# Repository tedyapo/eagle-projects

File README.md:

# eagle-projects

this is my private repo of PCB designs in Eagle

you probably should not use these for anything unless I have specifically pointed you to a design

I DO NOT support this repository for anyone other than myself

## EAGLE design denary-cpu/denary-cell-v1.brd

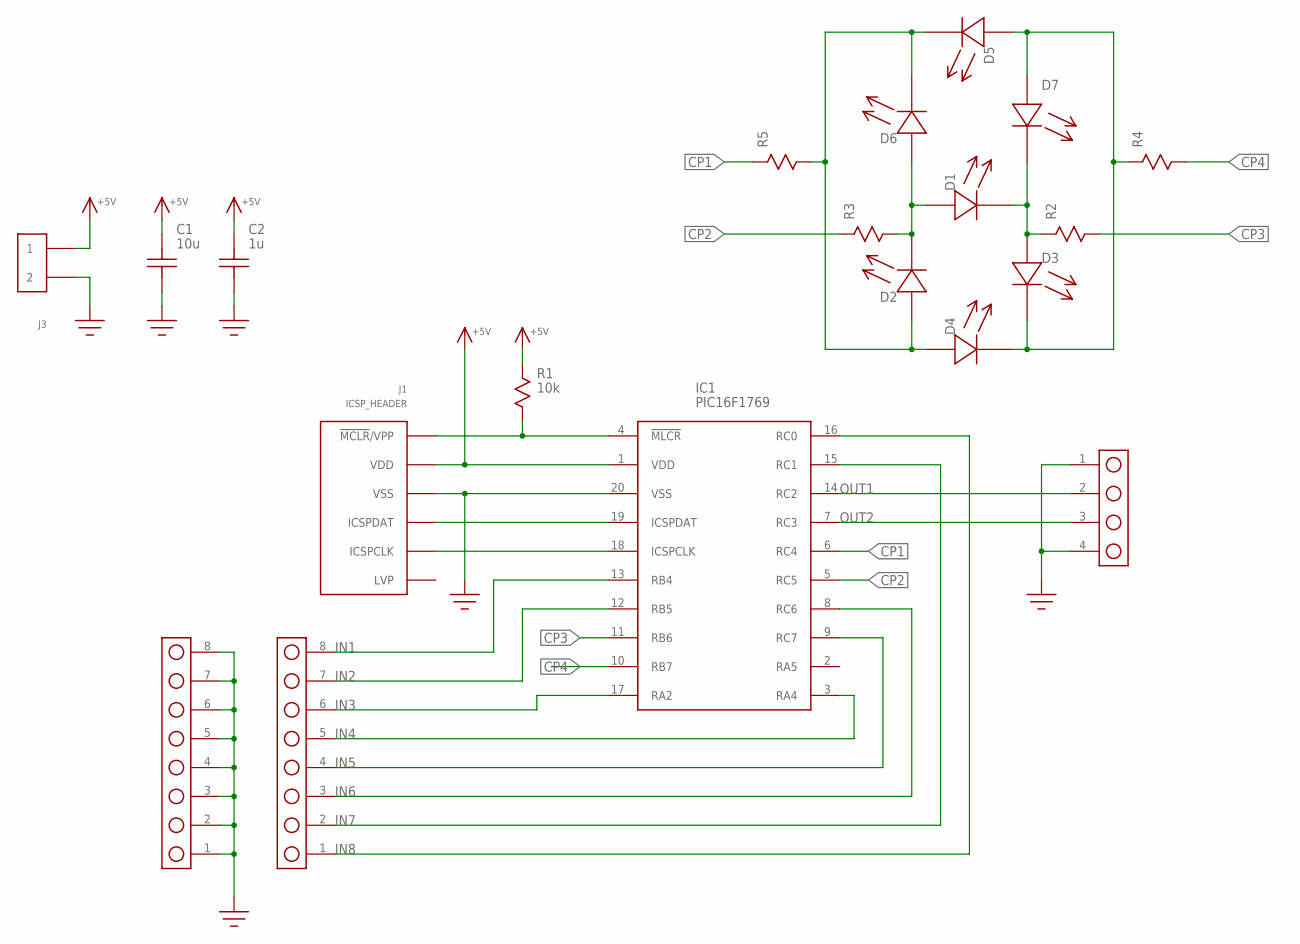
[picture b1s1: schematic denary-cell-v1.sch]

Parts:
C1: 10u; 1206
C2: 1u; C0603
D1, D2, D3, D4, D5, D6, D7: LED; LED_0603
IC1: PIC16F1769; SOIC-20W
J1: ICSP_HEADER; HEADER_6PIN
J2: HEADER_4PIN
J3: HEADER_2PIN
J4, J5: HEADER_8PIN; HEADER_8_PIN
R1: 10k; R0603
R2, R3, R4, R5: R0603

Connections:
+5V: C1.P$2, C2.P$2, IC1.1 (VDD), J1.2 (VDD), J3.1, R1.P$1
CP1: IC1.6 (RC4), R5.P$1
CP2: IC1.5 (RC5), R3.P$1
CP3: IC1.11 (RB6), R2.P$2
CP4: IC1.10 (RB7), R4.P$2
GND: C1.P$1, C2.P$1, IC1.20 (VSS), J1.3 (VSS), J2.1, J2.4, J3.2, J5.1, J5.2, J5.3, J5.4, J5.5, J5.6, J5.7, J5.8
IN1: IC1.13 (RB4), J4.8
IN2: IC1.12 (RB5), J4.7
IN3: IC1.17 (RA2), J4.6
IN4: IC1.3 (RA4), J4.5
IN5: IC1.9 (RC7), J4.4
IN6: IC1.8 (RC6), J4.3
IN7: IC1.15 (RC1), J4.2
IN8: IC1.16 (RC0), J4.1
unnamed: IC1.4 (!MLCR!), J1.1 (!MCLR!/VPP), R1.P$2
unnamed: D2.A, D4.A, D5.C, D6.C, R5.P$2
unnamed: IC1.19 (ICSPDAT), J1.4 (ICSPDAT)
unnamed: IC1.18 (ICSPCLK), J1.5 (ICSPCLK)
unnamed: D1.A, D2.C, D6.A, R3.P$2
unnamed: D1.C, D3.A, D7.C, R2.P$1
unnamed: D3.C, D4.C, D5.A, D7.A, R4.P$1
OUT1: IC1.14 (RC2), J2.2
OUT2: IC1.7 (RC3), J2.3

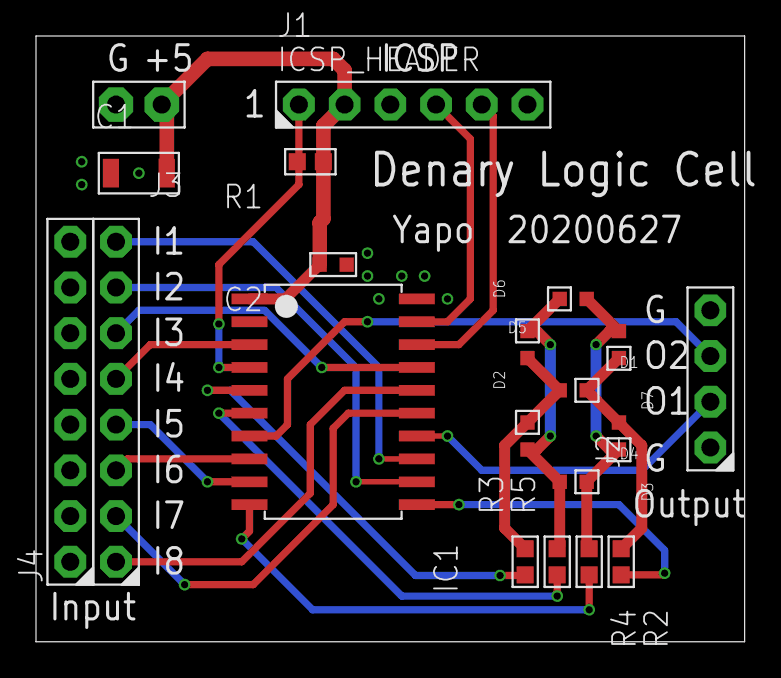
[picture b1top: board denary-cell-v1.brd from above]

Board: 2 copper layers, 39.4 x 33.7 mm, 20 parts (0 on the bottom side), 23 nets.

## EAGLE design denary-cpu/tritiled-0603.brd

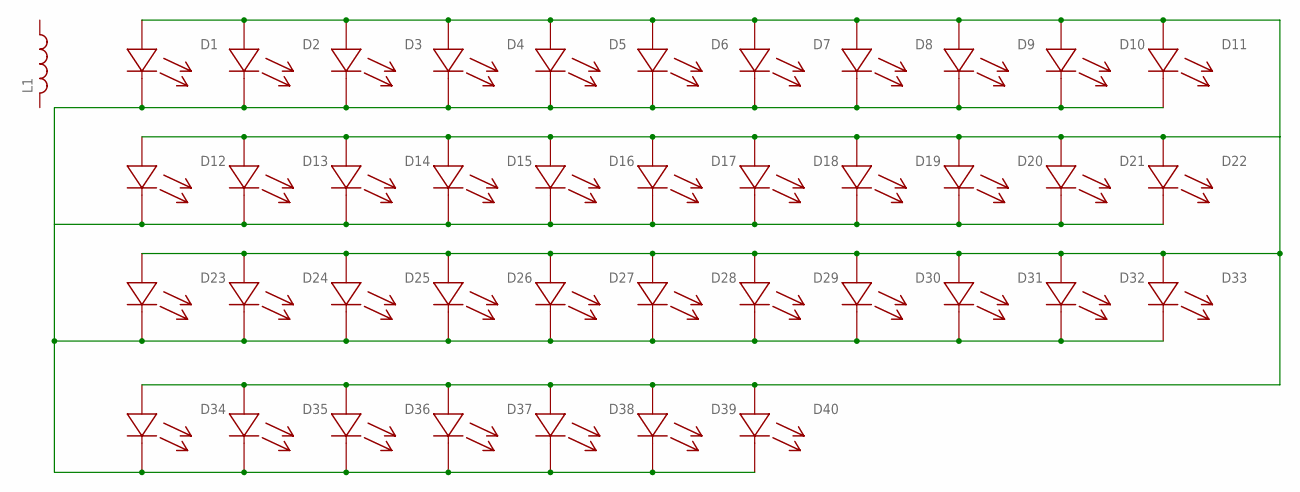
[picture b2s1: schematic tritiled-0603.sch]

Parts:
D1, D2, D3, D4, D5, D6, D7, D8, D9, D10, D11, D12, D13, D14, D15, D16, D17, D18, D19, D20, D21, D22, D23, D24, D25, D26, D27, D28, D29, D30, D31, D32, D33, D34, D35, D36, D37, D38, D39, D40: LED; LED_0603
L1: SRR6028_INDUCTOR

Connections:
unnamed: D1.C, D2.C, D3.C, D4.C, D5.C, D6.C, D7.C, D8.C, D9.C, D10.C, D11.C, D12.C, D13.C, D14.C, D15.C, D16.C, D17.C, D18.C, D19.C, D20.C, D21.C, D22.C, D23.C, D24.C, D25.C, D26.C, D27.C, D28.C, D29.C, D30.C, D31.C, D32.C, D33.C, D34.C, D35.C, D36.C, D37.C, D38.C, D39.C, D40.C
unnamed: D1.A, D2.A, D3.A, D4.A, D5.A, D6.A, D7.A, D8.A, D9.A, D10.A, D11.A, D12.A, D13.A, D14.A, D15.A, D16.A, D17.A, D18.A, D19.A, D20.A, D21.A, D22.A, D23.A, D24.A, D25.A, D26.A, D27.A, D28.A, D29.A, D30.A, D31.A, D32.A, D33.A, D34.A, D35.A, D36.A, D37.A, D38.A, D39.A, D40.A

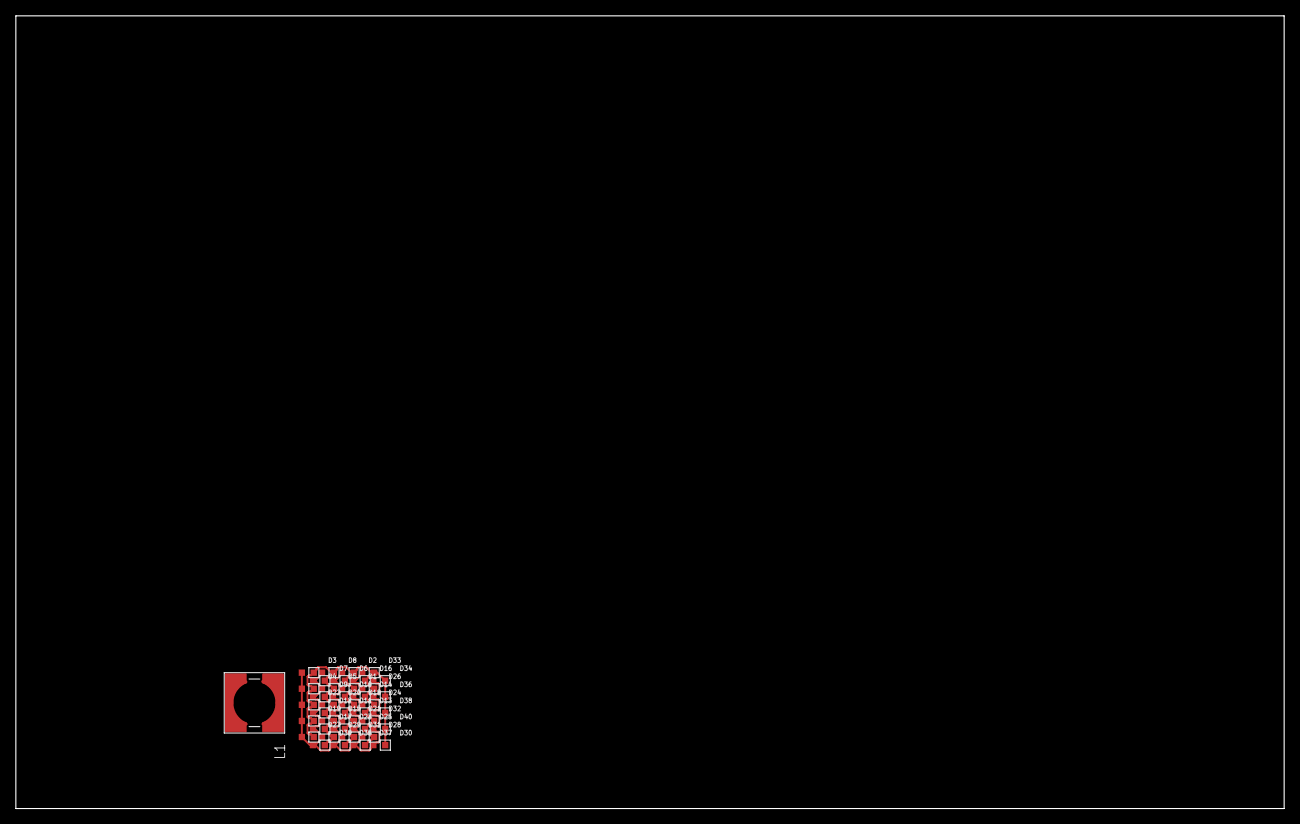
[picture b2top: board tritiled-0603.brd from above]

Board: 2 copper layers, 160.0 x 100.0 mm, 41 parts (0 on the bottom side), 2 nets.

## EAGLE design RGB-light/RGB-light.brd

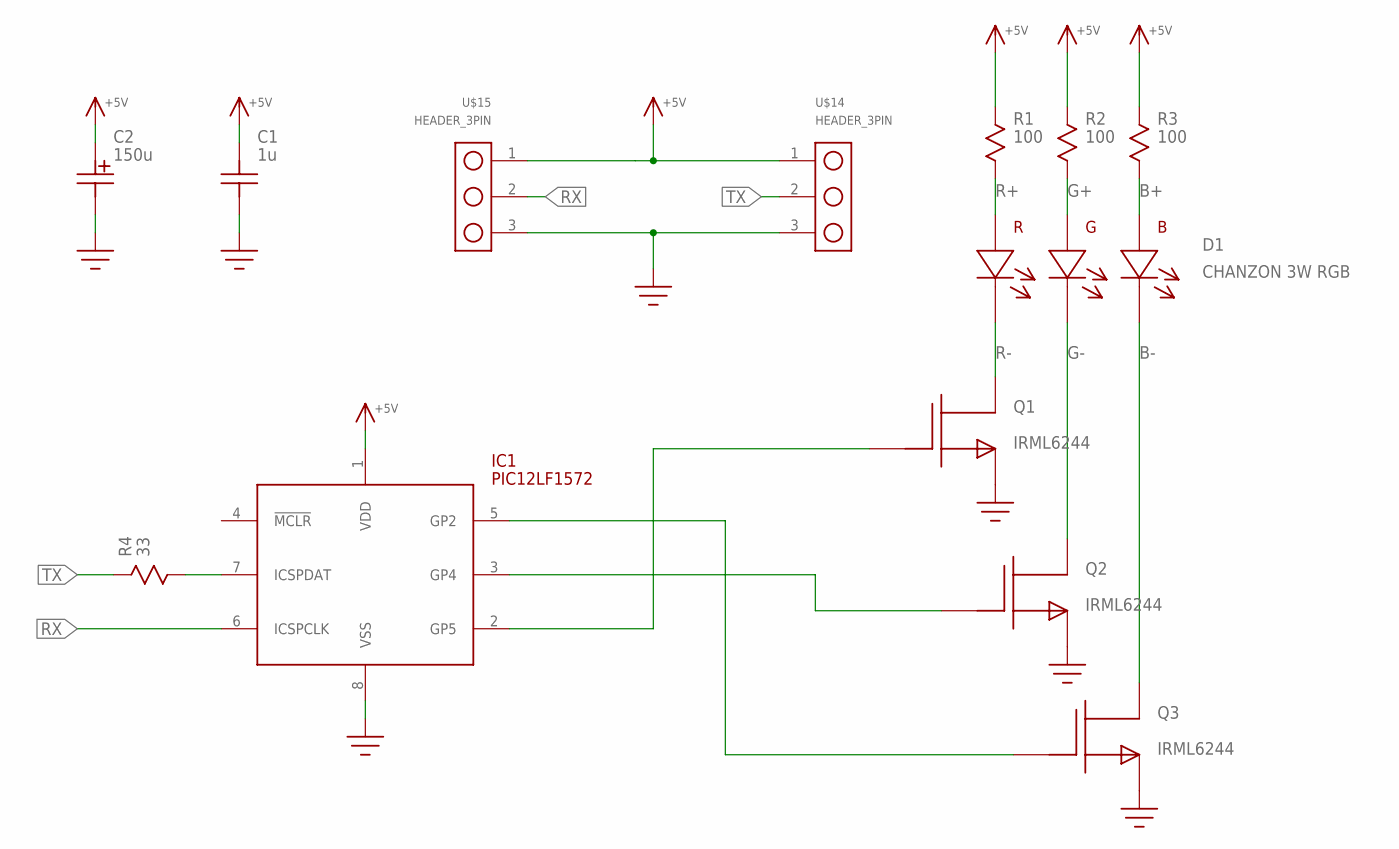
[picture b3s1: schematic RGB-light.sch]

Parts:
C1: 1u; C0603
C2: 150u; C-TANTALUM-CODE-C
D1: CHANZON 3W RGB; LED_3W_RGB
IC1: PIC12LF1572; SOIC8
Q1, Q2, Q3: IRML6244; SOT-23
R1, R2, R3: 100; R1206
R4: 33; R0603
U$14, U$15: HEADER_3PIN

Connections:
+5V: C1.P$2, C2.+, IC1.1 (VDD), R1.P$1, R2.P$1, R3.P$1, U$14.1, U$15.1
B+: D1.B+ (B-A), R3.P$2
B-: D1.B- (B-C), Q3.3 (D)
G+: D1.G+ (G-A), R2.P$2
G-: D1.G- (G-C), Q2.3 (D)
GND: C1.P$1, C2.-, IC1.8 (VSS), Q1.2 (S), Q2.2 (S), Q3.2 (S), U$14.3, U$15.3
unnamed: IC1.7 (ICSPDAT), R4.P$2
unnamed: IC1.5 (GP2), Q3.1 (G)
unnamed: IC1.3 (GP4), Q2.1 (G)
unnamed: IC1.2 (GP5), Q1.1 (G)
R+: D1.R+ (R-A), R1.P$2
R-: D1.R- (R-C), Q1.3 (D)
RX: IC1.6 (ICSPCLK), U$15.2
TX: R4.P$1, U$14.2

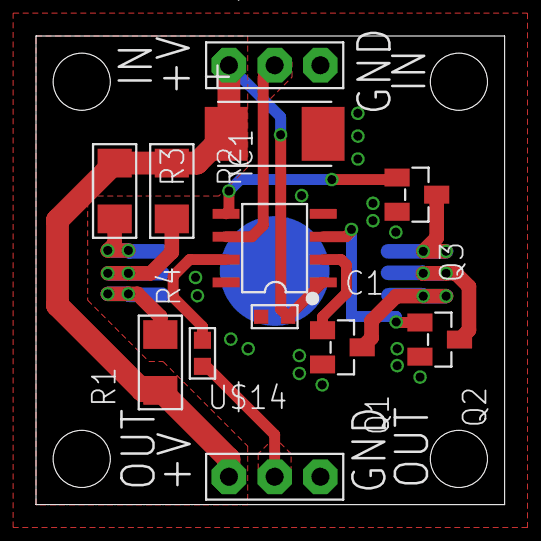
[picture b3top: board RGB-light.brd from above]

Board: 2 copper layers, 26.0 x 26.0 mm, 13 parts (1 on the bottom side), 14 nets.

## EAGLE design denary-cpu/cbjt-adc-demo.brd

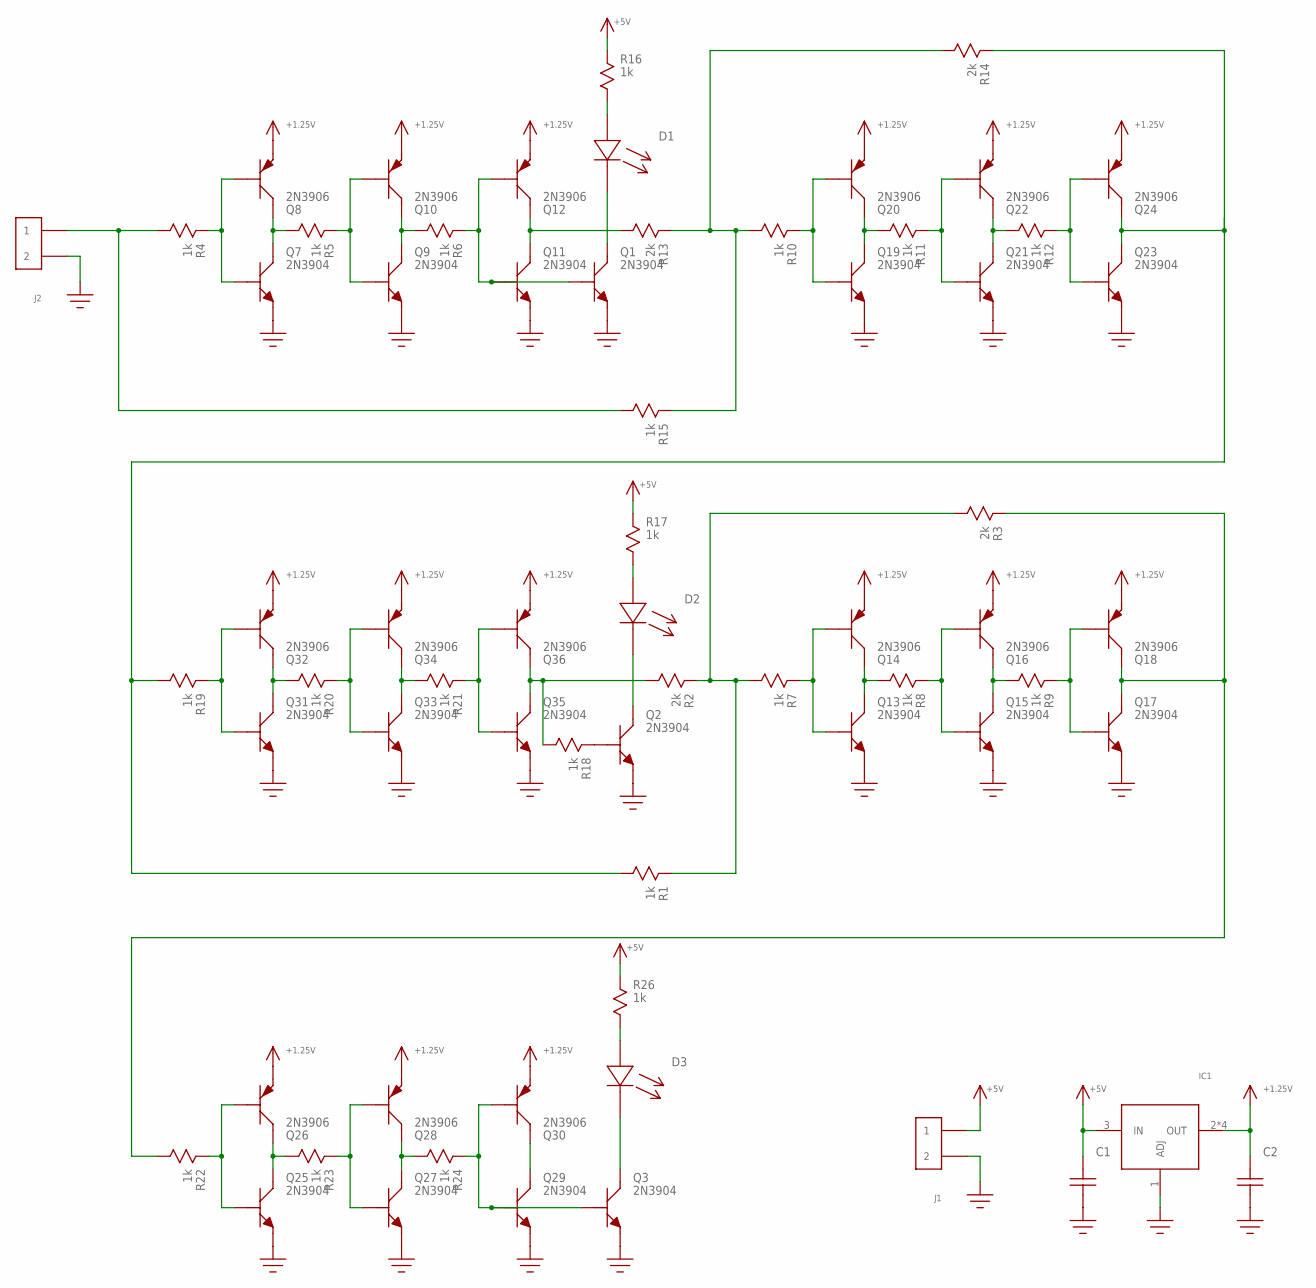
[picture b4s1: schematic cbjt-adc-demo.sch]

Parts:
C1, C2: C100MIL; C-100MIL
D1, D2, D3: LED5MM; LED-5MM
IC1: LM317; TO-220
J1, J2: HEADER_2PIN
Q1, Q2, Q3, Q7, Q9, Q11, Q13, Q15, Q17, Q19, Q21, Q23, Q25, Q27, Q29, Q31, Q33, Q35: 2N3904; TO-92
Q8, Q10, Q12, Q14, Q16, Q18, Q20, Q22, Q24, Q26, Q28, Q30, Q32, Q34, Q36: 2N3906; TO-92
R1, R4, R5, R6, R7, R8, R9, R10, R11, R12, R15, R16, R17, R18, R19, R20, R21, R22, R23, R24, R26: 1k; R-0.25W
R2, R3, R13, R14: 2k; R-0.25W

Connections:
+1.25V: C2.P$2, IC1.2 (OUT), IC1.HS@1 (OUT), IC1.HS@2 (OUT), IC1.HS@3 (OUT), Q8.1 (E), Q10.1 (E), Q12.1 (E), Q14.1 (E), Q16.1 (E), Q18.1 (E), Q20.1 (E), Q22.1 (E), Q24.1 (E), Q26.1 (E), Q28.1 (E), Q30.1 (E), Q32.1 (E), Q34.1 (E), Q36.1 (E)
+5V: C1.P$2, IC1.3 (IN), J1.1, R16.P$1, R17.P$1, R26.P$1
GND: C1.P$1, C2.P$1, IC1.1 (ADJ), J1.2, J2.2, Q1.1 (E), Q2.1 (E), Q3.1 (E), Q7.1 (E), Q9.1 (E), Q11.1 (E), Q13.1 (E), Q15.1 (E), Q17.1 (E), Q19.1 (E), Q21.1 (E), Q23.1 (E), Q25.1 (E), Q27.1 (E), Q29.1 (E), Q31.1 (E), Q33.1 (E), Q35.1 (E)
unnamed: R1.P$1, R2.P$1, R3.P$2, R7.P$2
unnamed: D1.C, Q1.3 (C)
unnamed: D1.A, R16.P$2
unnamed: Q2.2 (B), R18.P$1
unnamed: D2.C, Q2.3 (C)
unnamed: D2.A, R17.P$2
unnamed: Q7.3 (C), Q8.3 (C), R5.P$2
unnamed: Q7.2 (B), Q8.2 (B), R4.P$1
unnamed: Q9.3 (C), Q10.3 (C), R6.P$2
unnamed: Q9.2 (B), Q10.2 (B), R5.P$1
unnamed: Q11.3 (C), Q12.3 (C), R13.P$2
unnamed: Q1.2 (B), Q11.2 (B), Q12.2 (B), R6.P$1
unnamed: Q13.3 (C), Q14.3 (C), R8.P$2
unnamed: Q13.2 (B), Q14.2 (B), R7.P$1
unnamed: Q15.3 (C), Q16.3 (C), R9.P$2
unnamed: Q15.2 (B), Q16.2 (B), R8.P$1
unnamed: Q17.3 (C), Q18.3 (C), R3.P$1, R22.P$2
unnamed: Q17.2 (B), Q18.2 (B), R9.P$1
unnamed: Q19.3 (C), Q20.3 (C), R11.P$2
unnamed: Q19.2 (B), Q20.2 (B), R10.P$1
unnamed: Q21.3 (C), Q22.3 (C), R12.P$2
unnamed: Q21.2 (B), Q22.2 (B), R11.P$1
unnamed: Q23.3 (C), Q24.3 (C), R1.P$2, R14.P$1, R19.P$2
unnamed: Q23.2 (B), Q24.2 (B), R12.P$1
unnamed: R10.P$2, R13.P$1, R14.P$2, R15.P$1
unnamed: J2.1, R4.P$2, R15.P$2
unnamed: Q25.3 (C), Q26.3 (C), R23.P$2
unnamed: Q25.2 (B), Q26.2 (B), R22.P$1
unnamed: Q27.3 (C), Q28.3 (C), R24.P$2
unnamed: Q27.2 (B), Q28.2 (B), R23.P$1
unnamed: Q29.3 (C), Q30.3 (C)
unnamed: Q3.2 (B), Q29.2 (B), Q30.2 (B), R24.P$1
unnamed: Q31.3 (C), Q32.3 (C), R20.P$2
unnamed: Q31.2 (B), Q32.2 (B), R19.P$1
unnamed: Q33.3 (C), Q34.3 (C), R21.P$2
unnamed: Q33.2 (B), Q34.2 (B), R20.P$1
unnamed: Q35.3 (C), Q36.3 (C), R2.P$2, R18.P$2
unnamed: Q35.2 (B), Q36.2 (B), R21.P$1
unnamed: D3.C, Q3.3 (C)
unnamed: D3.A, R26.P$2

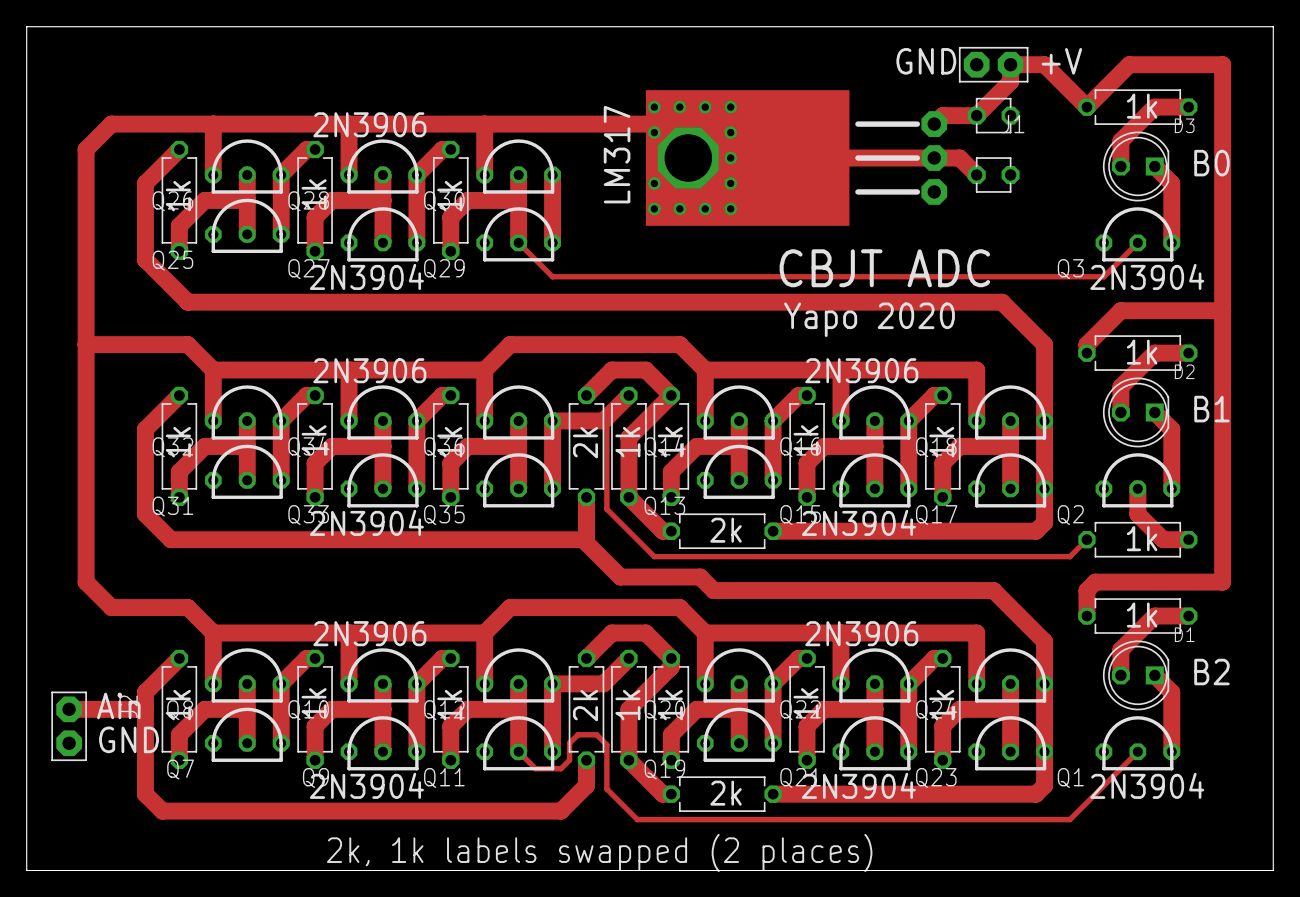
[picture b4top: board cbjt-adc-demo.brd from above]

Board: 2 copper layers, 93.3 x 63.2 mm, 66 parts (0 on the bottom side), 43 nets.

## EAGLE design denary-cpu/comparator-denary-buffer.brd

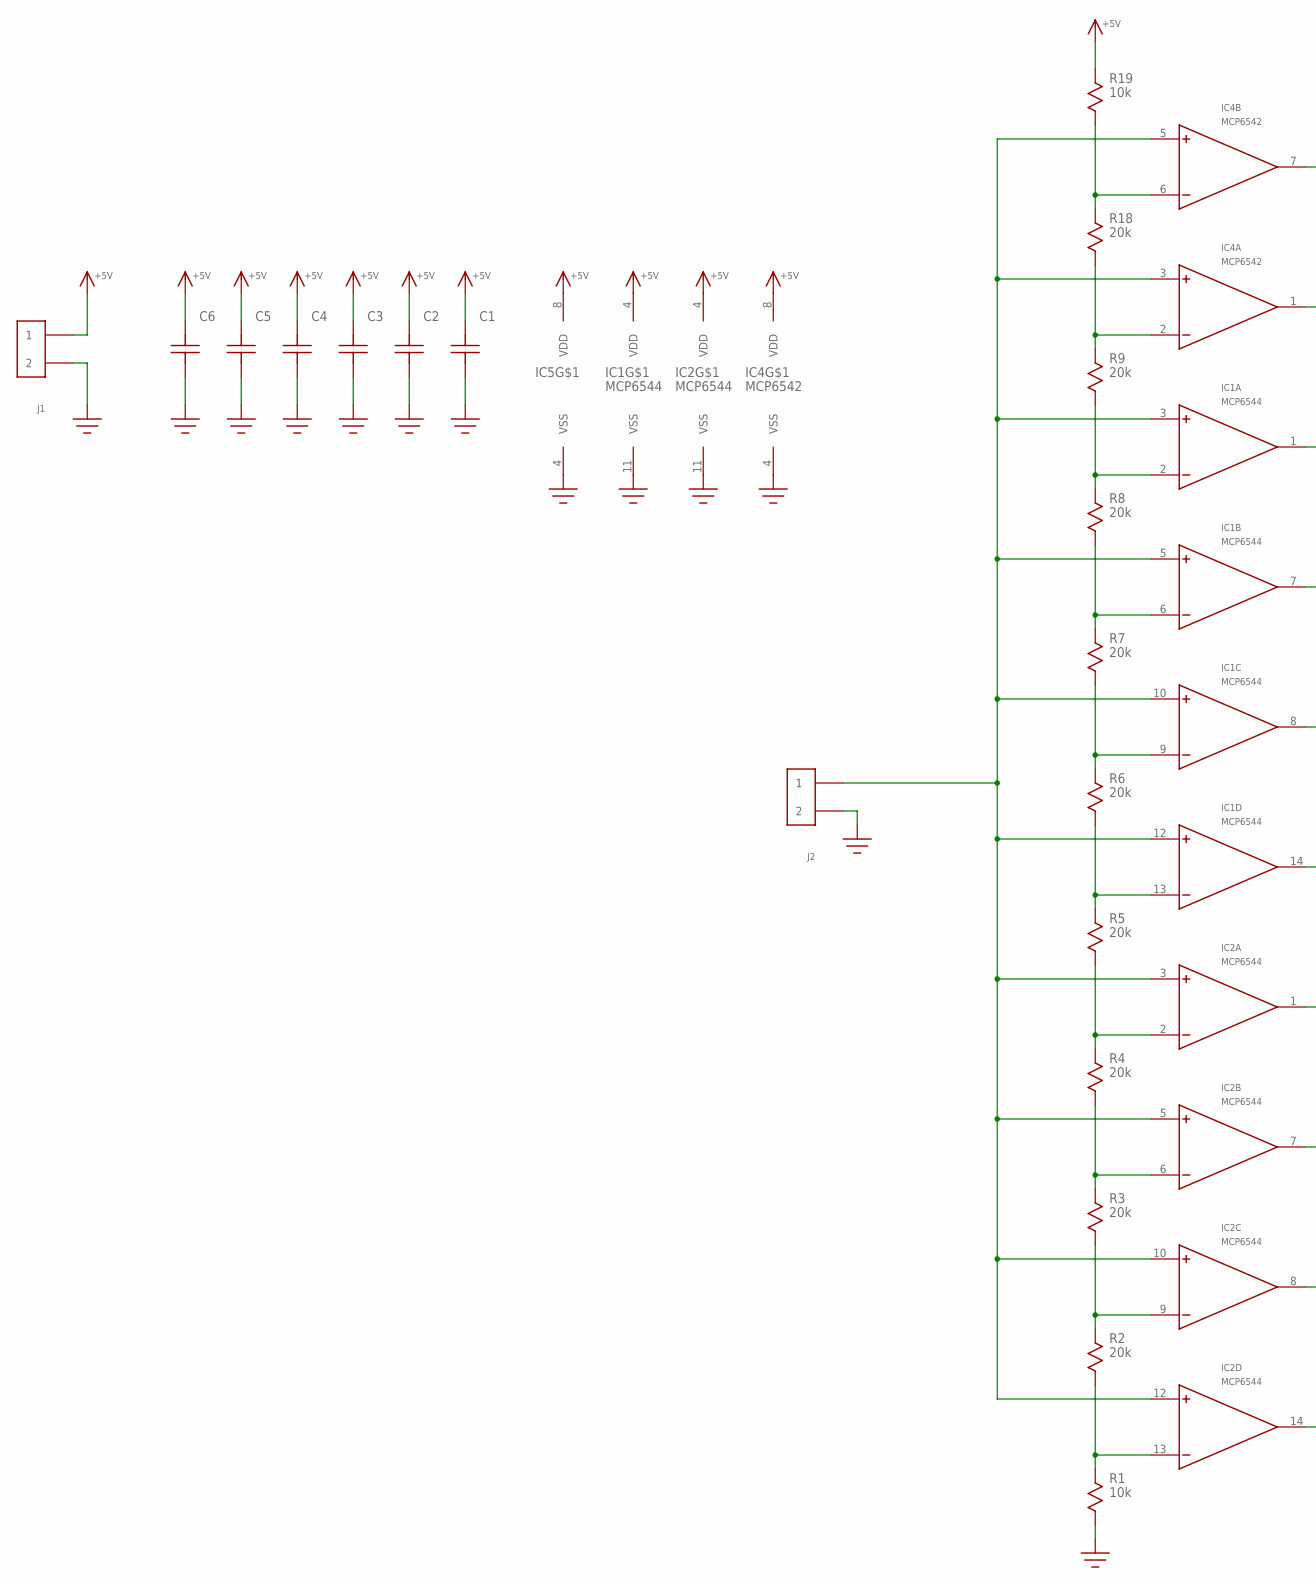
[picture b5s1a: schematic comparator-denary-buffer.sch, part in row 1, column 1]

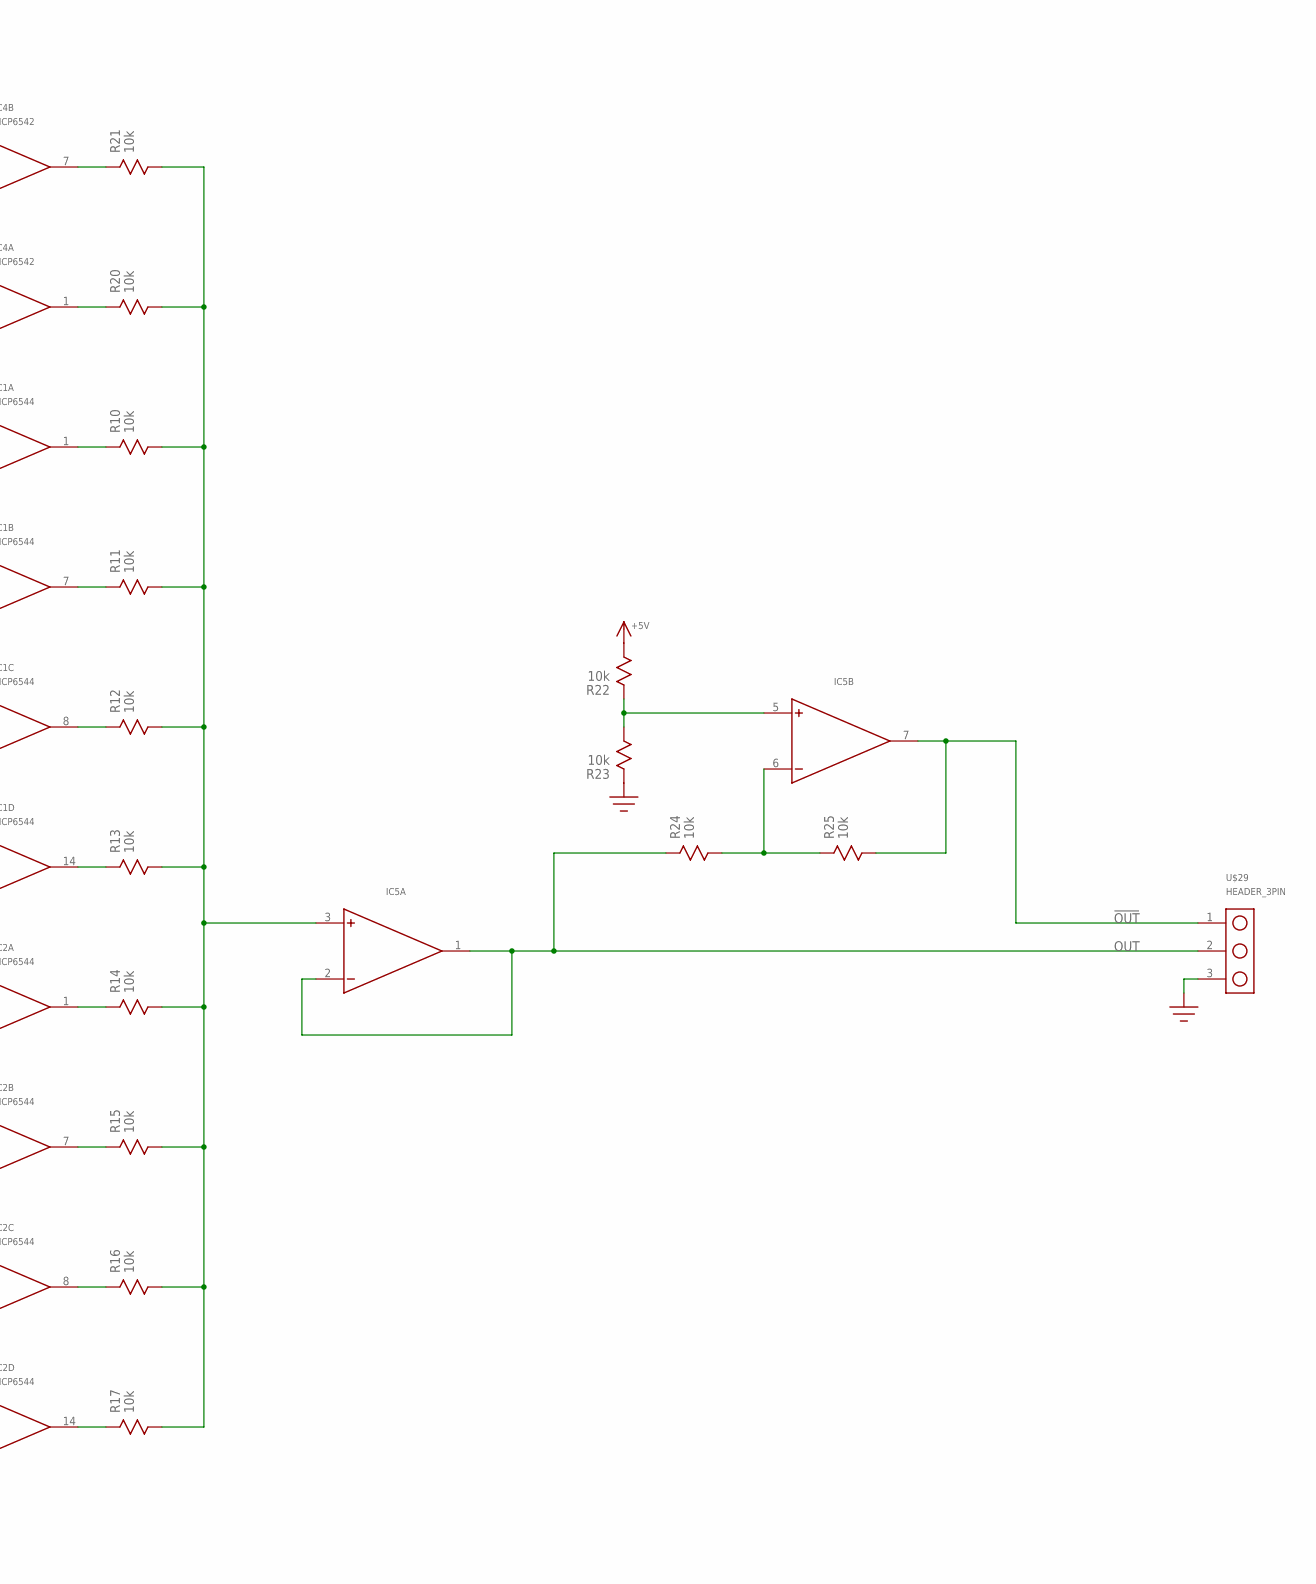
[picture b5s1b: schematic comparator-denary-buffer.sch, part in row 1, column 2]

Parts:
C1, C2, C3, C4, C5: C0603
C6: C1206; 1206
IC1, IC2: MCP6544; SOIC-14
IC4: MCP6542; SOIC8
IC5: MCP6L02; SOIC8
J1, J2: HEADER_2PIN
R1, R10, R11, R12, R13, R14, R15, R16, R17, R19, R20, R21, R22, R23, R24, R25: 10k; R0603
R2, R3, R4, R5, R6, R7, R8, R9, R18: 20k; R0603
U$29: HEADER_3PIN

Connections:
!OUT!: IC5.7 (OUT), R25.P$2, U$29.1
+5V: C1.P$2, C2.P$2, C3.P$2, C4.P$2, C5.P$2, C6.P$2, IC1.4 (VDD), IC2.4 (VDD), IC4.8 (VDD), IC5.8 (VDD), J1.1, R19.P$1, R22.P$2
GND: C1.P$1, C2.P$1, C3.P$1, C4.P$1, C5.P$1, C6.P$1, IC1.11 (VSS), IC2.11 (VSS), IC4.4 (VSS), IC5.4 (VSS), J1.2, J2.2, R1.P$2, R23.P$1, U$29.3
unnamed: IC2.13 (-), R1.P$1, R2.P$2
unnamed: IC2.14 (OUT), R17.P$1
unnamed: IC2.9 (-), R2.P$1, R3.P$2
unnamed: IC2.8 (OUT), R16.P$1
unnamed: IC2.6 (-), R3.P$1, R4.P$2
unnamed: IC2.2 (-), R4.P$1, R5.P$2
unnamed: IC1.13 (-), R5.P$1, R6.P$2
unnamed: IC1.9 (-), R6.P$1, R7.P$2
unnamed: IC1.6 (-), R7.P$1, R8.P$2
unnamed: IC2.7 (OUT), R15.P$1
unnamed: IC2.1 (OUT), R14.P$1
unnamed: IC1.14 (OUT), R13.P$1
unnamed: IC1.8 (OUT), R12.P$1
unnamed: IC1.2 (-), R8.P$1, R9.P$2
unnamed: IC1.7 (OUT), R11.P$1
unnamed: IC1.1 (OUT), R10.P$1
unnamed: IC5.3 (+), R10.P$2, R11.P$2, R12.P$2, R13.P$2, R14.P$2, R15.P$2, R16.P$2, R17.P$2, R20.P$2, R21.P$2
unnamed: IC4.2 (-), R9.P$1, R18.P$2
unnamed: IC4.6 (-), R18.P$1, R19.P$2
unnamed: IC4.7 (OUT), R21.P$1
unnamed: IC4.1 (OUT), R20.P$1
unnamed: IC5.5 (+), R22.P$1, R23.P$2
unnamed: IC5.6 (-), R24.P$2, R25.P$1
OUT: IC5.1 (OUT), IC5.2 (-), R24.P$1, U$29.2
VIN: IC1.3 (+), IC1.5 (+), IC1.10 (+), IC1.12 (+), IC2.3 (+), IC2.5 (+), IC2.10 (+), IC2.12 (+), IC4.3 (+), IC4.5 (+), J2.1

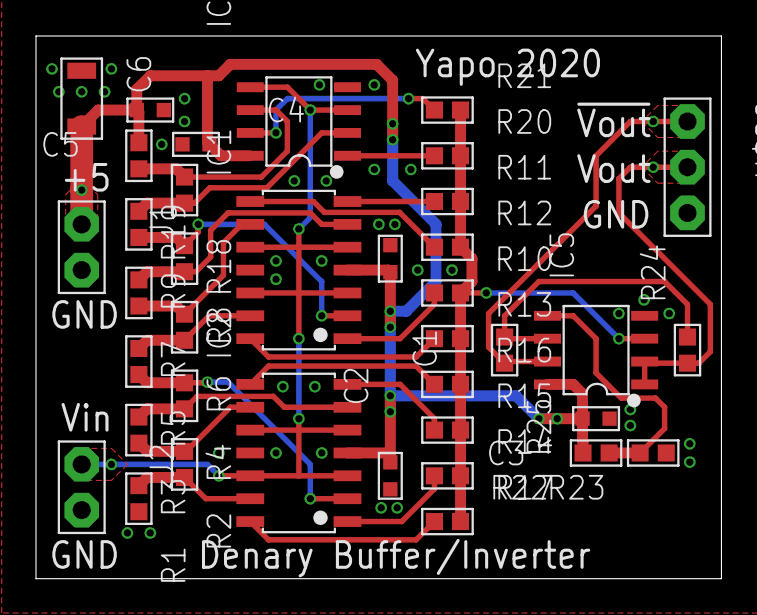
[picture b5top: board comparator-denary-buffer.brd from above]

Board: 2 copper layers, 38.1 x 30.1 mm, 38 parts (0 on the bottom side), 28 nets.

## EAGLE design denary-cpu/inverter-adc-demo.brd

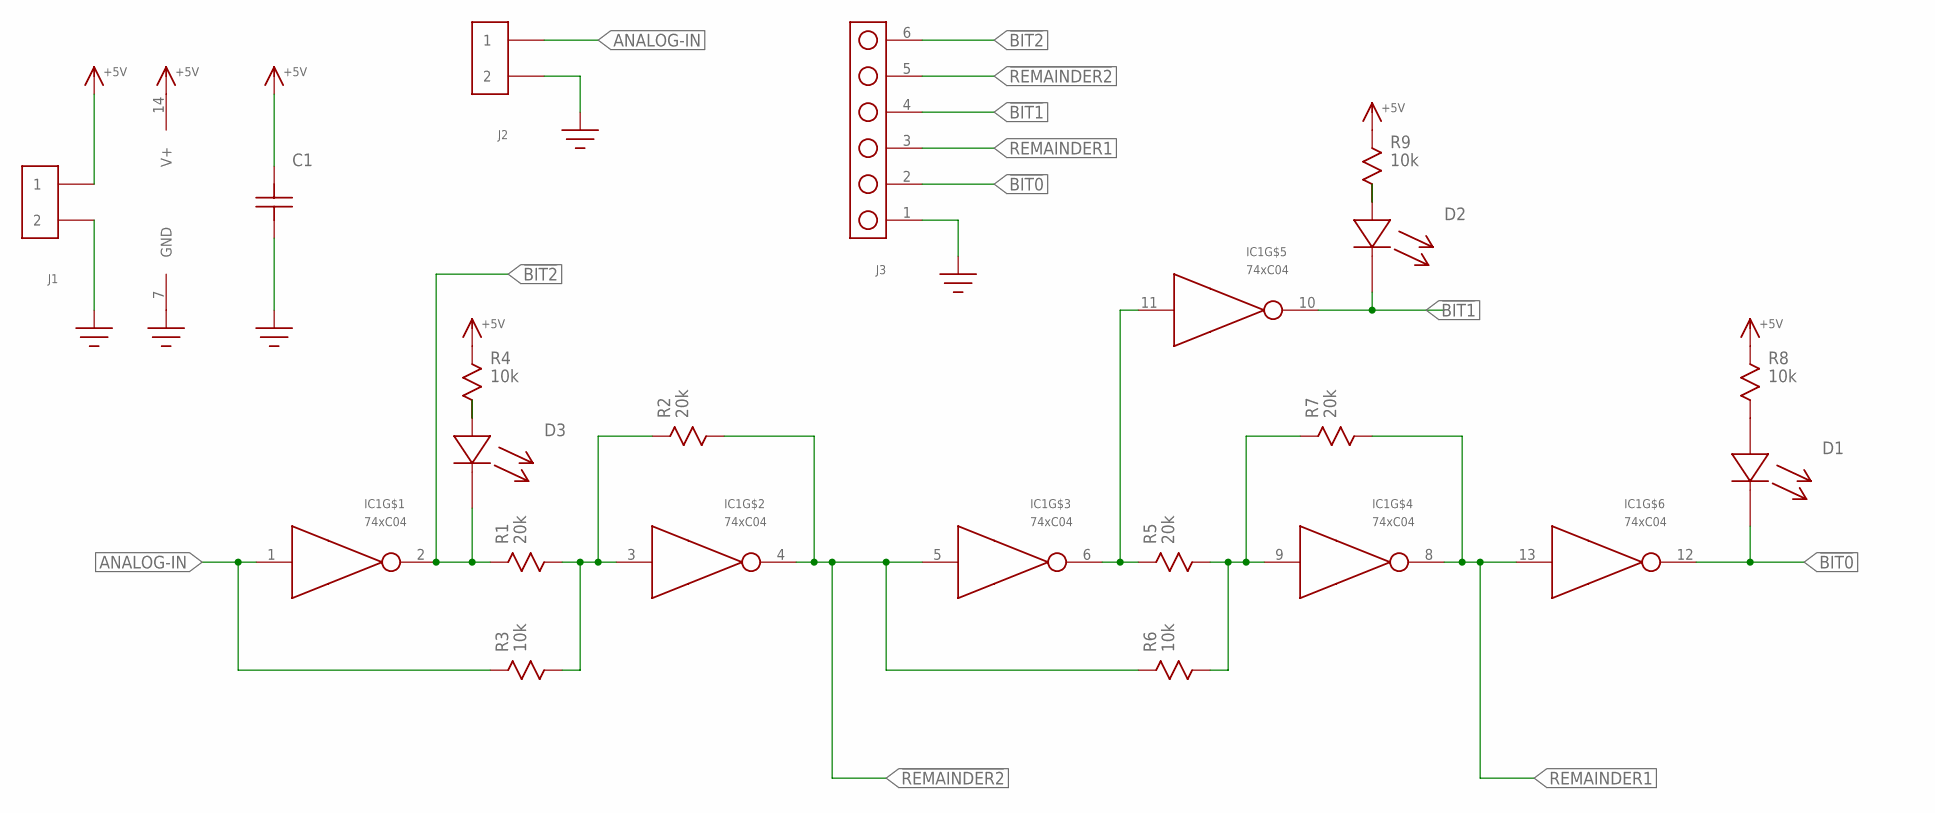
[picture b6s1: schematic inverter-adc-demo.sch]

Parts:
C1: C100MIL; C-100MIL
D1, D2, D3: LED5MM; LED-5MM
IC1: 74xC04; DIP14
J1, J2: HEADER_2PIN
J3: HEADER_6PIN
R1, R2, R5, R7: 20k; R-0.25W
R3, R4, R6, R8, R9: 10k; R-0.25W

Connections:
!BIT0!: D1.C, IC1.12 (OUT), J3.2
!BIT1!: D2.C, IC1.10 (OUT), J3.4
!BIT2!: D3.C, IC1.2 (OUT), J3.6, R1.P$1
!REMAINDER2!: IC1.4 (OUT), IC1.5 (IN), J3.5, R2.P$2, R6.P$1
+5V: C1.P$2, IC1.14 (V+), J1.1, R4.P$1, R8.P$1, R9.P$1
ANALOG-IN: IC1.1 (IN), J2.1, R3.P$1
GND: C1.P$1, IC1.7 (GND), J1.2, J2.2, J3.1
unnamed: IC1.3 (IN), R1.P$2, R2.P$1, R3.P$2
unnamed: IC1.6 (OUT), IC1.11 (IN), R5.P$1
unnamed: IC1.9 (IN), R5.P$2, R6.P$2, R7.P$1
unnamed: D3.A, R4.P$2
unnamed: D1.A, R8.P$2
unnamed: D2.A, R9.P$2
REMAINDER1: IC1.8 (OUT), IC1.13 (IN), J3.3, R7.P$2

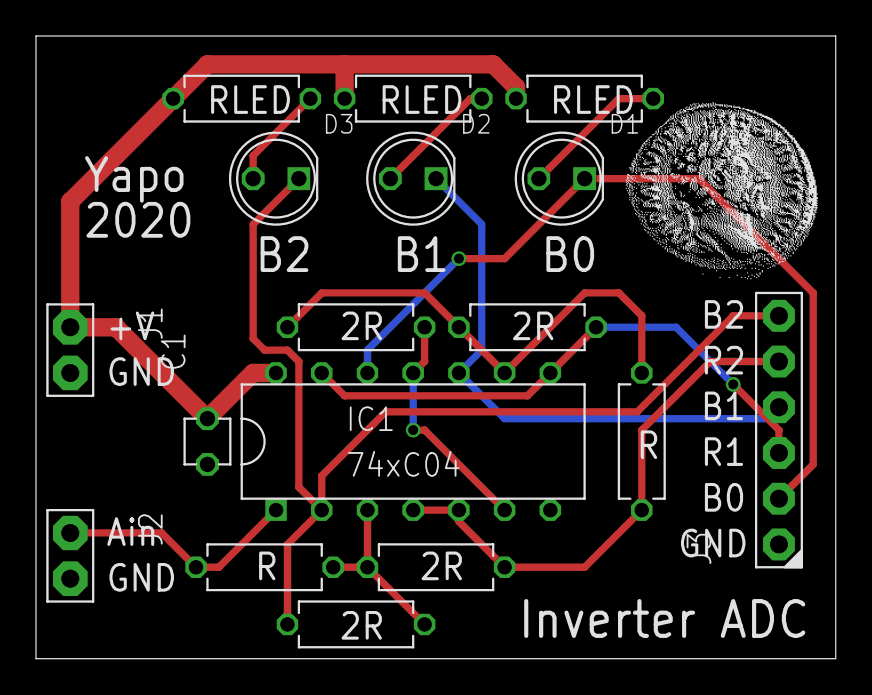
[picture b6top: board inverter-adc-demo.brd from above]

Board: 2 copper layers, 44.4 x 34.6 mm, 17 parts (0 on the bottom side), 14 nets.

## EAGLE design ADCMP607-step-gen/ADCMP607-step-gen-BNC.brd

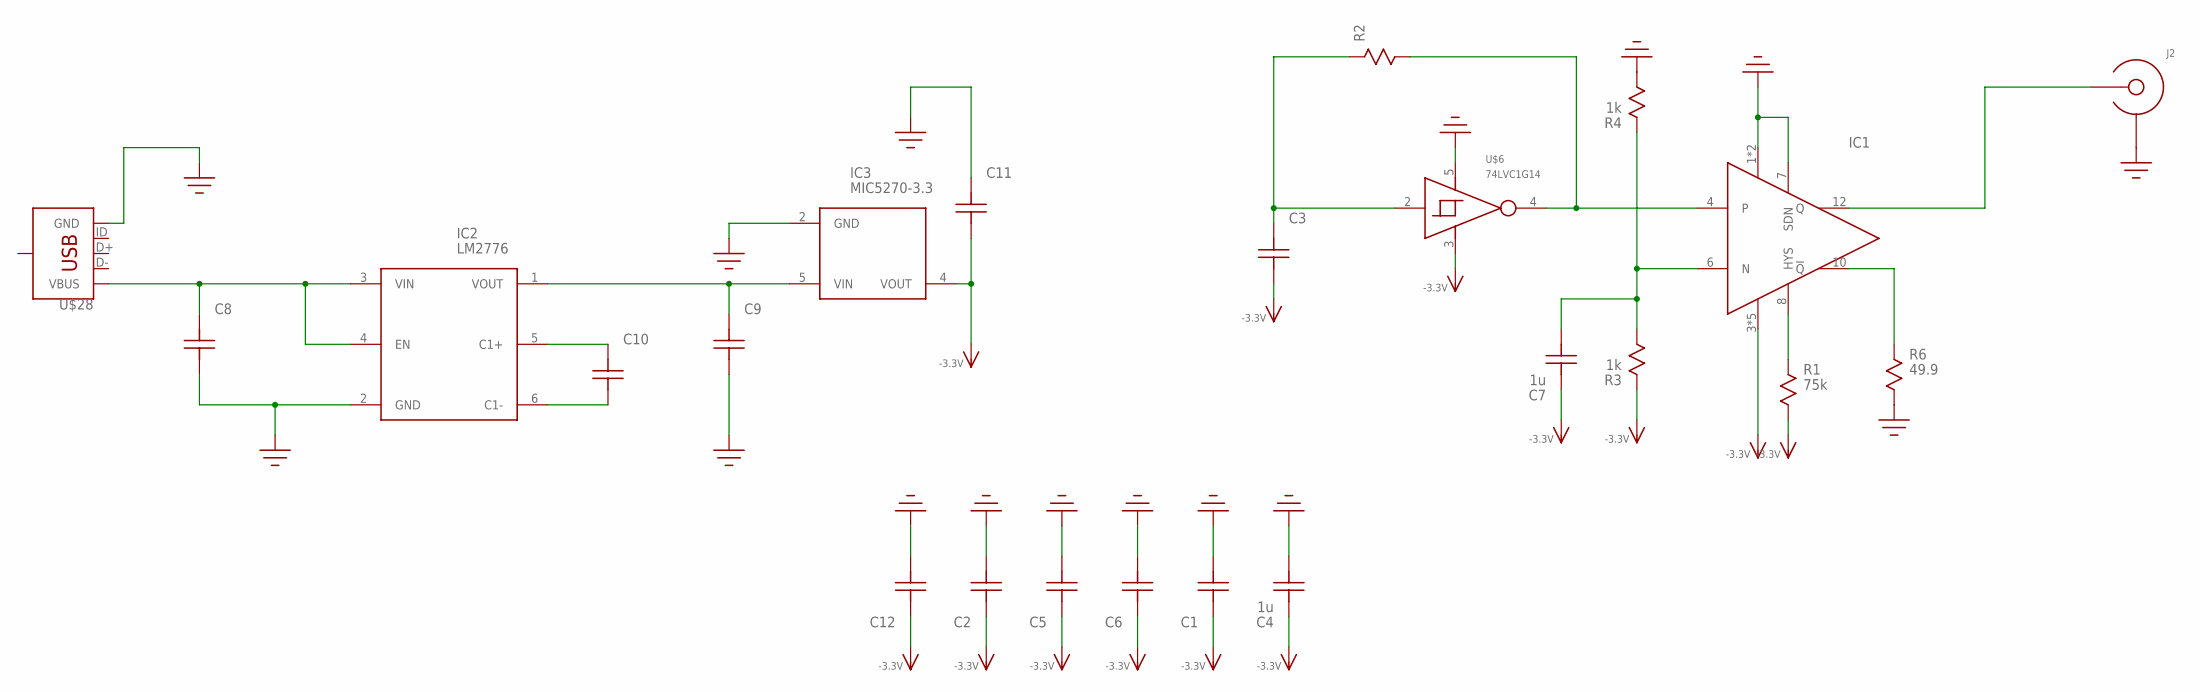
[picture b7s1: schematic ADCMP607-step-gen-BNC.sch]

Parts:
C1, C2, C3, C5, C6, C10, C12: C0603
C4, C7: 1u; C0603
C8, C9, C11: C1206; 1206
IC1: ADCMP607; QFN12-3X3
IC2: LM2776; SOT23-6
IC3: MIC5270-3.3; SOT23-5
J2: BNC_MALE_PCB
R1: 75k; R0603
R2: R0603
R3, R4: 1k; R0603
R6: 49.9; R0603
U$6: 74LVC1G14; SOT23-5
U$28: USB_MICRO_LEGS; USB_MICRO_LEGS_2

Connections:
-3.3V: C1.P$2, C2.P$2, C3.P$1, C4.P$2, C5.P$2, C6.P$2, C7.P$2, C11.P$1, C12.P$2, IC1.3 (VEE), IC1.5 (VEE), IC1.9 (VEE), IC1.11 (VEE), IC1.EP (VEE), IC3.4 (VOUT), R1.P$2, R3.P$1, U$6.3 (GND)
GND: C1.P$1, C2.P$1, C4.P$1, C5.P$1, C6.P$1, C8.P$1, C9.P$1, C11.P$2, C12.P$1, IC1.1 (VCC), IC1.2 (VCC), IC1.7 (SDN), IC2.2 (GND), IC3.2 (GND), J2.SHIELD@1 (SHIELD), J2.SHIELD@2 (SHIELD), J2.SHIELD@3 (SHIELD), J2.SHIELD@4 (SHIELD), R4.P$2, R6.P$2, U$6.5 (VCC), U$28.GND
unnamed: IC1.4, R2.P$2, U$6.4 (OUT)
unnamed: IC1.8 (HYS), R1.P$1
unnamed: IC1.12 (Q), J2.CENTER
unnamed: IC1.10 (!Q!), R6.P$1
unnamed: C3.P$2, R2.P$1, U$6.2 (IN)
unnamed: C7.P$1, IC1.6 (N), R3.P$2, R4.P$1
unnamed: C8.P$2, IC2.3 (VIN), IC2.4 (EN), U$28.VBUS
unnamed: C10.P$2, IC2.5 (C1+)
unnamed: C10.P$1, IC2.6 (C1-)
unnamed: C9.P$2, IC2.1 (VOUT), IC3.5 (VIN)

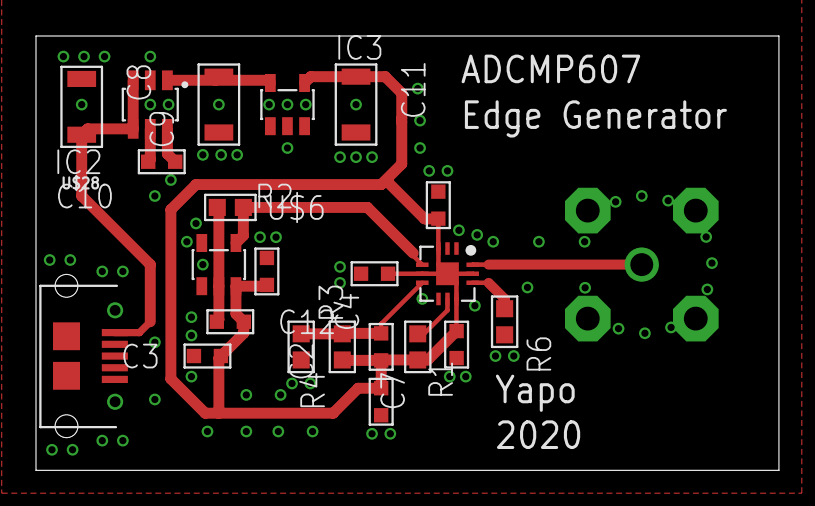
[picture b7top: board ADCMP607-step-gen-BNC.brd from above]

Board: 2 copper layers, 41.3 x 24.1 mm, 23 parts (0 on the bottom side), 12 nets.
